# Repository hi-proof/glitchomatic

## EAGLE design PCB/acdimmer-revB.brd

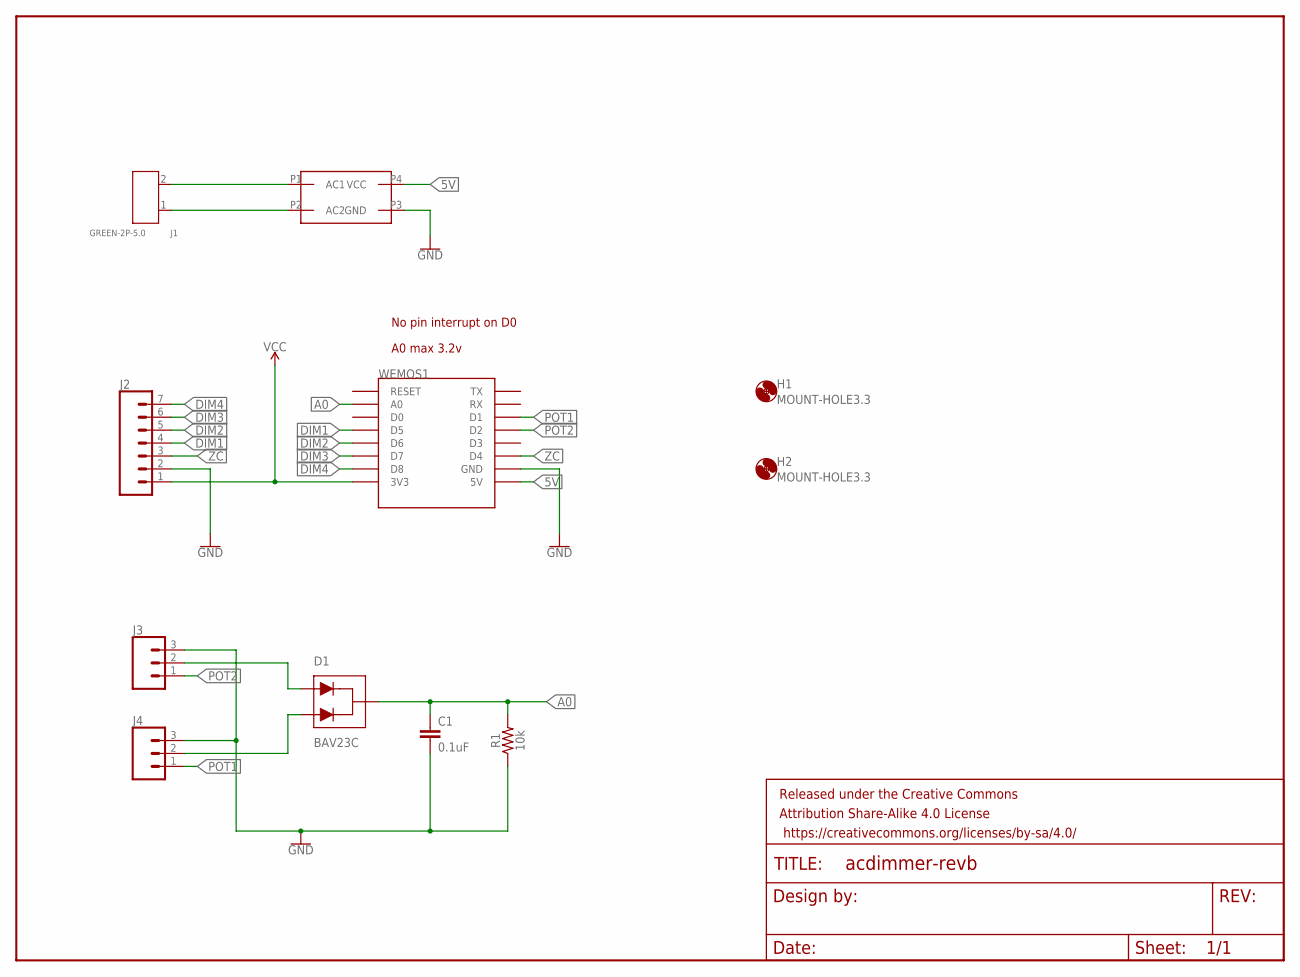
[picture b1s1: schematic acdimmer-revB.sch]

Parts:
C1: 0.1uF; 0603
D1: BAV23C; SOT23-3
FRAME1: FRAME-LETTERNO_PACKAGE; DUMMY
H1, H2: MOUNT-HOLE3.3; 3,3
J1: GREEN-2P-5.0; H2-5.0-10.5X8.0MM
J2: CONN_07NO_SILK; 1X07_NO_SILK
J3, J4: CONN_03SCREW; SCREWTERMINAL-3.5MM-3
R1: 10k; 0603
U$1: ACDC5V
WEMOS1: WEMOS-D1-MINI

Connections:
5V: U$1.P4 (VCC), WEMOS1.5V
A0: C1.1, D1.3 (C), R1.2, WEMOS1.A0
DIM1: J2.4, WEMOS1.D5
DIM2: J2.5, WEMOS1.D6
DIM3: J2.6, WEMOS1.D7
DIM4: J2.7, WEMOS1.D8
GND: C1.2, J2.2, J3.3, J4.3, R1.1, U$1.P3 (GND), WEMOS1.GND
unnamed: J1.2, U$1.P1 (AC1)
unnamed: J1.1, U$1.P2 (AC2)
unnamed: D1.1 (A1), J3.2
unnamed: D1.2 (A2), J4.2
POT1: J4.1, WEMOS1.D1
POT2: J3.1, WEMOS1.D2
VCC: J2.1, WEMOS1.3V3
ZC: J2.3, WEMOS1.D4

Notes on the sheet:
No pin interrupt on D0
A0 max 3.2v

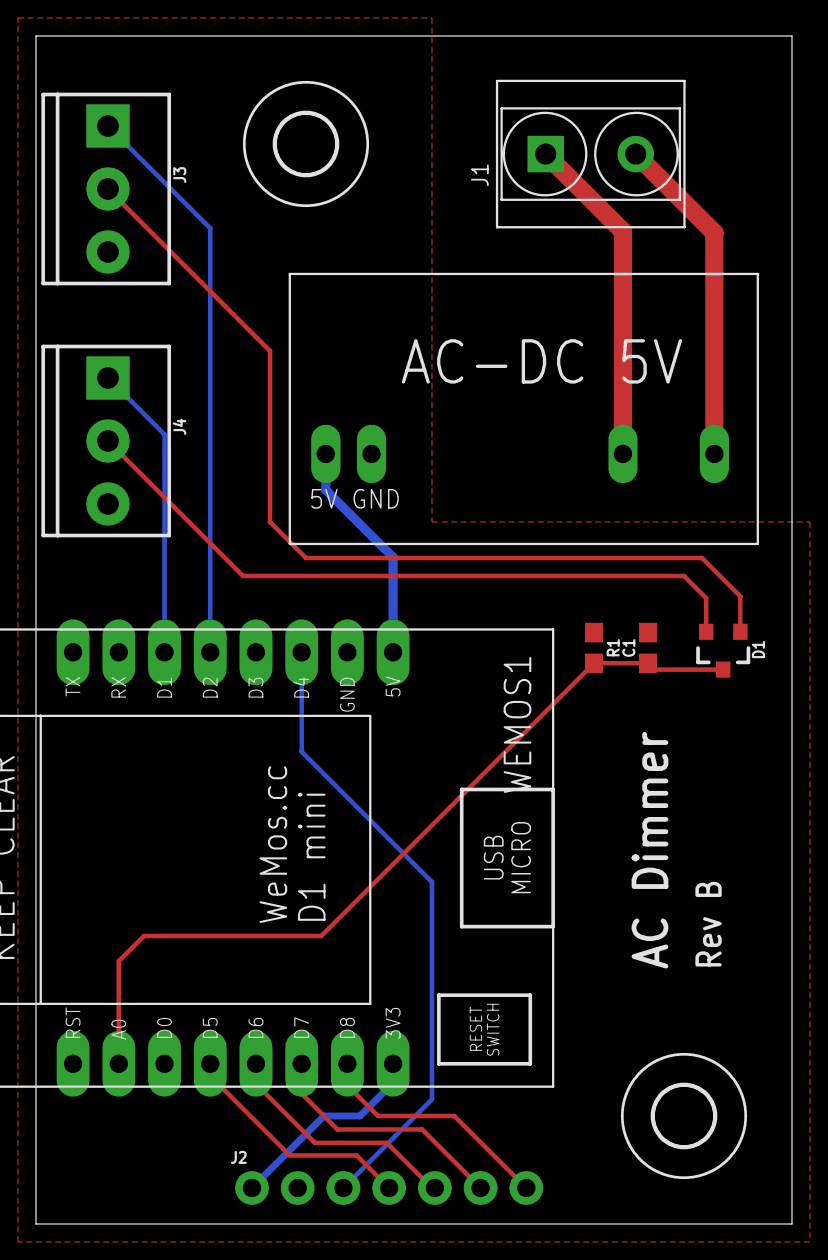
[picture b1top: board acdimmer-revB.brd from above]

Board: 2 copper layers, 42.0 x 66.0 mm, 12 parts (0 on the bottom side), 15 nets.

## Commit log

2019-11-09 Initial commit with PCBs and code
2019-11-12 Wip for 4 pin version. doesn't work yet

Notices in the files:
parts and their libraries:
SparkFun-DiscreteSemi: Licensing: Creative Commons ShareAlike 4.0 International - https://creativecommons.org/licenses/by-sa/4.0
SparkFun-Aesthetics: Released under the Creative Commons Attribution Share-Alike 4.0 License
SparkFun-Aesthetics: https://creativecommons.org/licenses/by-sa/4.0
